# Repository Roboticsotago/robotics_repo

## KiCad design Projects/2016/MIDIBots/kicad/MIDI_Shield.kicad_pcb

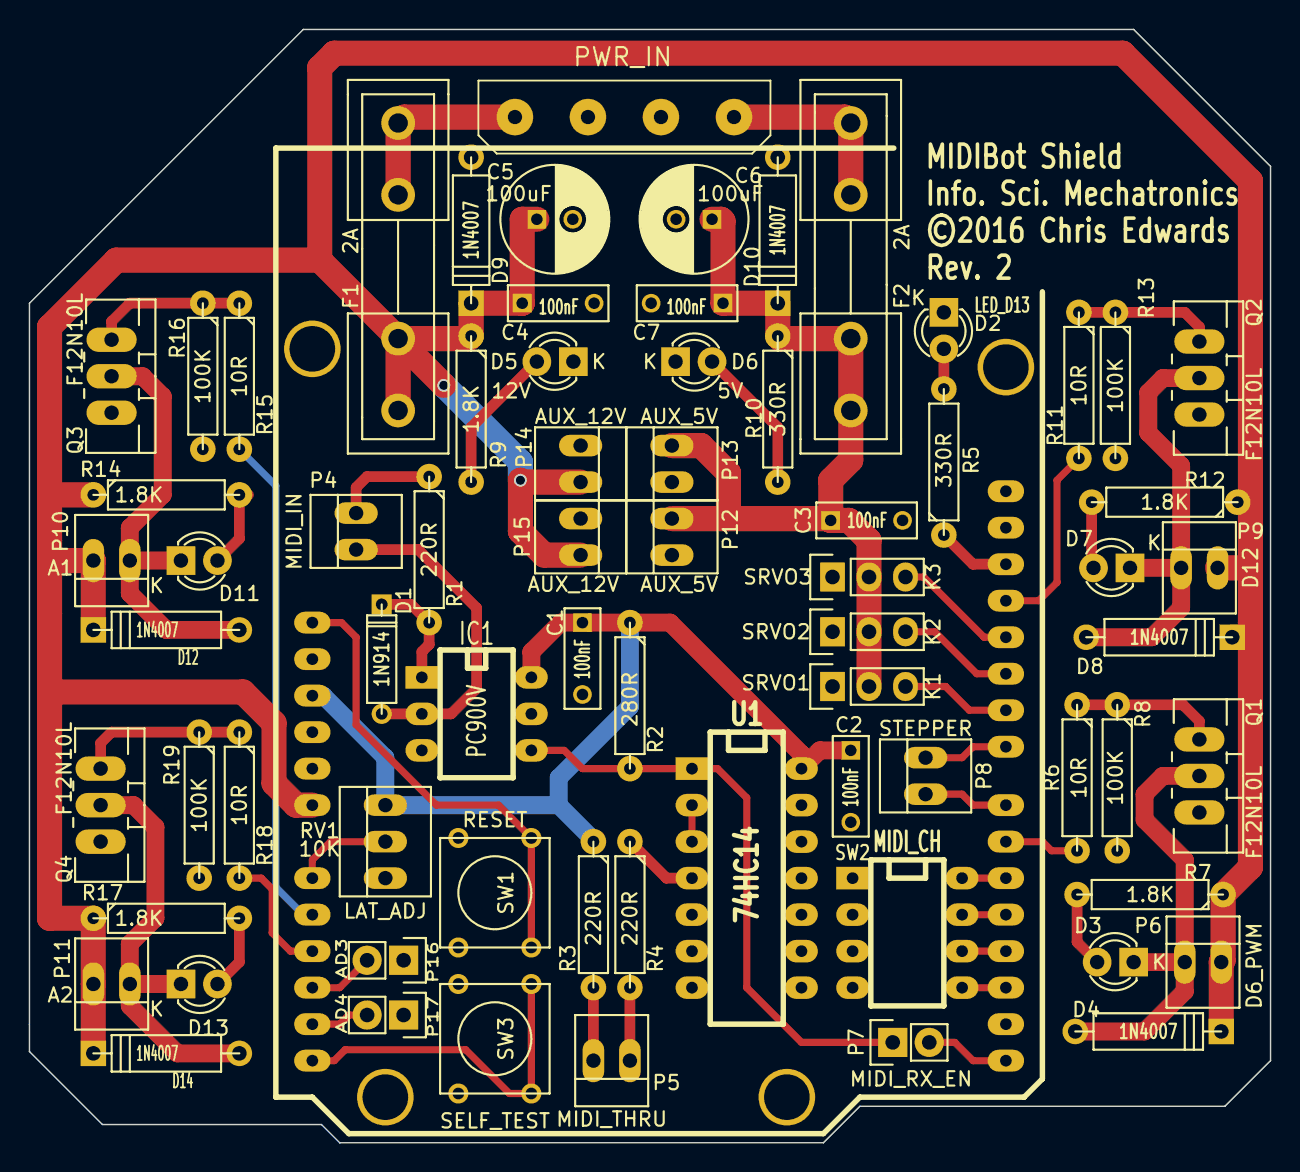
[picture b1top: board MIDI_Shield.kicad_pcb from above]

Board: 2 copper layers, 86.4 x 77.5 mm, 71 parts (0 on the bottom side), 49 nets.

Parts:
C1, C2, C3, C4, C7: 100nF; C_Rect_L7_W2.5_P5
C5, C6: 100uF; C_Radial_D7.5_L11.2_P2.5
D1: 1N914; D3
D2: LED_D13; LED-3MM
D3, D7, D11, D13: LED; LED-3MM
D4, D8, D9, D10, D12, D14: 1N4007; D4
D5: 12V; LED-3MM
D6: 5V; LED-3MM
F1, F2: 2A; Fuseholder5x20_horiz_open_inline_Type-I
IC1: PC900V; DIP-6__300_ELL
K1: SRVO1; Pin_Header_Straight_1x03
K2: SRVO2; Pin_Header_Straight_1x03
K3: SRVO3; Pin_Header_Straight_1x03
P3: PWR_IN; xess-MOLEX-8981-04P
P4: MIDI_IN; PINHEAD1-2
P5: MIDI_THRU; PINHEAD1-2
P6: D6_PWM; PINHEAD1-2
P7: MIDI_RX_EN; Pin_Header_Straight_1x02
P8: STEPPER; PINHEAD1-2
P9: D12; PINHEAD1-2
P10: A1; PINHEAD1-2
P11: A2; PINHEAD1-2
P12, P13: AUX_12V; PINHEAD1-2
P14, P15: AUX_5V; PINHEAD1-2
P16: AD3; Pin_Header_Straight_1x02
P17: AD4; Pin_Header_Straight_1x02
Q1, Q2, Q3, Q4: F12N10L; TO-220_Neutral123_Vertical_LargePads
R1, R3, R4: 220R; R4-LARGE_PADS
R2: 280R; R4-LARGE_PADS
R5, R10: 330R; R4-LARGE_PADS
R6, R11, R15, R18: 10R; R4-LARGE_PADS
R7, R9, R12, R14, R17: 1.8K; R4-LARGE_PADS
R8, R13, R16, R19: 100K; R4-LARGE_PADS
RV1: 10K; PINHEAD1-3
SHIELD1: ARDUINO_SHIELD
SW1: RESET; SW_PUSH_SMALL
SW2: MIDI_CH; DIP-8__300_ELL
SW3: SELF_TEST; SW_PUSH_SMALL
U1: 74HC14; DIP-14__300_ELL

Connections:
+5V: C3.1, C6.1, C7.1, D10.1, F2.2, K1.2, K2.2, K3.2, P14.2, P15.2, R10.1
+12V: C4.1, C5.1, D4.1, D8.1, D9.1, D12.1, D14.1, F1.1, P6.2, P9.2, P10.2, P11.2, P12.2, P13.2, R7.1, R9.1, R12.1, R14.1, R17.1, SHIELD1.V_IN
/AD3: P16.2, SHIELD1.AD3
/AD4: P17.2, SHIELD1.AD4
/LATENCY_ADJ: RV1.2, SHIELD1.AD0
/LED_BUILTIN: R5.1, SHIELD1.13
/MIDI_CH_1x: SHIELD1.2, SW2.5
/MIDI_CH_2x: SHIELD1.3, SW2.6
/MIDI_CH_4x: SHIELD1.4, SW2.7
/MIDI_CH_8x: SHIELD1.5, SW2.8
/MIDI_IN_TTL: IC1.4, P7.1, R2.2, U1.1
/MOSFET_1_PWM: R6.2, SHIELD1.6
/MOSFET_2: R11.2, SHIELD1.12
/MOSFET_3: R15.2, SHIELD1.AD1
/MOSFET_4: R18.2, SHIELD1.AD2
/RESET: SHIELD1.RST, SW1.1
/SELF_TEST: SHIELD1.AD5, SW3.1
/SERVO_1: K1.3, SHIELD1.9
/SERVO_2: K2.3, SHIELD1.10
/SERVO_3: K3.3, SHIELD1.11
/STEPPER_DIR: P8.1, SHIELD1.7
/STEPPER_STEP: P8.2, SHIELD1.8
GND: C1.2, C2.2, C3.2, C4.2, C5.2, C6.2, C7.2, D2.1, D5.1, D6.1, D9.2, D10.2, IC1.5, K1.1, K2.1, K3.1, P3.2, P3.3, P12.1, P13.1, P14.1, P15.1, P16.1, P17.1, Q1.3, Q2.3, Q3.3, Q4.3, R8.2, R13.2, R16.2, R19.2, RV1.1, SHIELD1.GND1, SHIELD1.GND2, SHIELD1.GND3, SW1.2, SW2.1, SW2.2, SW2.3, SW2.4, SW3.2, U1.5, U1.7, U1.9, U1.11, U1.13
unnamed: D1.1, IC1.1, R1.2
unnamed: D1.2, IC1.2, P4.1
unnamed: D2.2, R5.2
unnamed: D3.1, D4.2, P6.1, Q1.2
unnamed: D3.2, R7.2
unnamed: D5.2, R9.2
unnamed: D6.2, R10.2
unnamed: D7.1, D8.2, P9.1, Q2.2
unnamed: D7.2, R12.2
unnamed: D11.1, D12.2, P10.1, Q3.2
unnamed: D11.2, R14.2
unnamed: D13.1, D14.2, P11.1, Q4.2
unnamed: D13.2, R17.2
unnamed: F1.2, P3.1
unnamed: F2.1, P3.4
unnamed: P4.2, R1.1
unnamed: P5.2, R3.2
unnamed: P5.1, R4.2
unnamed: P7.2, SHIELD1.0
unnamed: Q1.1, R6.1, R8.1
unnamed: Q2.1, R11.1, R13.1
unnamed: Q3.1, R15.1, R16.1
unnamed: Q4.1, R18.1, R19.1
unnamed: R4.1, U1.4
unnamed: U1.2, U1.3
VCC: C1.1, C2.1, IC1.6, R2.1, R3.1, RV1.3, SHIELD1.5V, U1.14

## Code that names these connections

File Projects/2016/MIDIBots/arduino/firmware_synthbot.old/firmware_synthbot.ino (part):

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	MIDI_4x_PIN = 4,
	MIDI_8x_PIN = 5,
	MOSFET_PWM_PIN = 6,
	SERVO_1_PIN = 9,
	SERVO_2_PIN = 10,
	SERVO_3_PIN = 11,
	MOSFET_2_PIN = 12,
	MOSFET_3_PIN = A1, /* not A3 as on the silkscreen! */
	MOSFET_4_PIN = A2, /* not A4 as on the silkscreen! */
	LED_PIN = 13,
	LATENCY_ADJUST_PIN = A0,
	SELF_TEST_PIN = A5
;

int
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	pinMode(MIDI_8x_PIN, INPUT_PULLUP);
	
	// Ditto for self-test button:
	pinMode(SELF_TEST_PIN, INPUT_PULLUP);
	
	// TODO: output pins (servos, MOSFETs, LED)
	pinMode(LED_PIN, OUTPUT); digitalWrite(LED_PIN, LOW);
	pinMode(MOSFET_PWM_PIN, OUTPUT); analogWrite(MOSFET_PWM_PIN, 0);
	pinMode(MOSFET_2_PIN, OUTPUT); digitalWrite(MOSFET_2_PIN, LOW);
	pinMode(MOSFET_3_PIN, OUTPUT); digitalWrite(MOSFET_3_PIN, LOW);
	pinMode(MOSFET_4_PIN, OUTPUT); digitalWrite(MOSFET_4_PIN, LOW);
	pinMode(SERVO_1_PIN, OUTPUT); digitalWrite(SERVO_1_PIN, LOW);
	pinMode(SERVO_2_PIN, OUTPUT); digitalWrite(SERVO_2_PIN, LOW);
	pinMode(SERVO_3_PIN, OUTPUT); digitalWrite(SERVO_3_PIN, LOW);
	
	// Initialise MIDI channel number according to DIP switch settings:
	read_MIDI_channel();
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	clearData();
	
	// Attach interrupt for self-test button and function:
//	attachInterrupt(digitalPinToInterrupt(SELF_TEST_PIN), self_test, FALLING);
	// Only available on certain pins?  Just poll in main loop instead.
	
	// Flash to indicate startup/ready:
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
void loop()
{
	if (!digitalRead(SELF_TEST_PIN)) {
		self_test();
	}
	process_MIDI();
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}

void test_button() {
	digitalWrite(LED_PIN, !digitalRead(SELF_TEST_PIN));
}

void test_flash_number() {
	if (!digitalRead(SELF_TEST_PIN)) {
		flash_number(3);
		delay(2000);
		flash_number(16);
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}

void test_MIDI_channel() {
	if (!digitalRead(SELF_TEST_PIN)) {
		read_MIDI_channel();
		Serial.println(MIDI_channel);
		flash_number(MIDI_channel);
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}

void test_MOSFETs() {
	if (!digitalRead(SELF_TEST_PIN)) {
		analogWrite(MOSFET_PWM_PIN, 64);
		digitalWrite(MOSFET_2_PIN, HIGH);
		digitalWrite(MOSFET_3_PIN, HIGH);
		digitalWrite(MOSFET_4_PIN, HIGH);
	} else {
		analogWrite(MOSFET_PWM_PIN, 0);
		digitalWrite(MOSFET_2_PIN, LOW);
		digitalWrite(MOSFET_3_PIN, LOW);
		digitalWrite(MOSFET_4_PIN, LOW);
	}
}

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	delay(250);
	digitalWrite(MOSFET_PWM_PIN, LOW);
	
	digitalWrite(MOSFET_2_PIN, HIGH);
	delay(250);
	digitalWrite(MOSFET_2_PIN, LOW);
	
	digitalWrite(MOSFET_3_PIN, HIGH);
	delay(250);
	digitalWrite(MOSFET_3_PIN, LOW);

	digitalWrite(MOSFET_4_PIN, HIGH);
	delay(250);
	digitalWrite(MOSFET_4_PIN, LOW);
}

void test_PWM() {
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
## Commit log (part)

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2017-06-11 Added Arduino Mega drilling pattern
2017-06-13 Updated IR sensor code to work with analog inputs.
2017-06-13 Added atan2() demo in C
2017-06-13 Added returncode (to avoid `make` throwing an error when building)
2017-06-14 Added Arduino version of the atan2() demo program
2017-06-14 Fixed castor shim height (after actually measuring the actual castor height and robot platform height!)
2017-06-15 SoccerBot kicker paddle: reduced hole size to help grip 3.5 mm machine screws
2017-06-15 Expanded to-do list, added a Pure Data patch demonstrating how to pipe data in from Arduino serial stream
2017-06-15 Stripped out Chris's code for determining IR ball angle and distance the students to fill in.
2017-06-15 Added some notes on the Raspberry Pi camera
2017-06-15 Refined dimensions of RPi camera housing
2017-06-16 Add DSPace Robot board mounting pattern
2017-06-16 SoccerBot block diagram added
2017-06-16 Added notes on the Power HD DSM44 digital servo motor
2017-06-16 SoccerBots: added simple kicker mounting hinge part
2017-06-16 Added prototype kicker linkage part
2017-06-17 Lengthened kicker paddle for top-mounted servo
2017-06-17 Corrected servo mount dimensions for DSM44 servo; rounded corners
2017-06-18 Added servo horn extension part
2017-06-19 Added Dspace motor intial controller
2017-06-19 Added initial design for replacement mount for Tamiya castor
2017-06-19 Servo mount: reduced servo mounting hole diameter
2017-06-20 Adjusted range of servo, serial changes
2017-06-20 Added cylindrical spacer for mounting the IR platform on the main chassis
2017-06-20 Reduced mounting hole size to suit M3 screws (hopefully)
2017-06-21 Added software pipeline for mega
2017-06-21 Renamed IR_test to Sensors
2017-06-21 Renamed motor control
2017-06-22 Removed redundant Dalek code in SoccerBot motor control script.
    Fixed indentation & attempted a fix of Servo toggle switch.
2017-06-22 Corrected spelling error :-D
2017-06-22 Updated magnetometer test to point towards any heading
2017-06-22 Changed camera res
2017-06-22 have debugging mode output less often
2017-06-22 Added range sensor to sensor program
2017-06-22 changed PWM thresholds
2017-06-22 changed deadzone thresholds.
2017-06-23 Added symbolic link
2017-06-23 Added wrapper script for running the Mega sensor cu pipeline (so it can be restarted by monit if necessary
2017-06-26 Added initial debriefing notes from the Otago 2017 regionals
2017-06-26 Added further explanation on motor KV rating
2017-06-27 Added separate program for camera calabration
2017-06-27 Added motor control for boris
2017-06-29 Some tidying of EEPROM doc
2017-06-29 Added (OLD) camera_calibration_state.py file from the netbook
2017-06-30 Added a few extras for Friday's plan
2017-06-30 Fixed range sensor behaviour (after setting jumpers and programming its EEPROM for passive PWM mode)
2017-06-30 Switching over to use Tcl-based read_sensors.tcl instead of cu; added message between main control patch (bot-specific) to motor-control.pd to command which serial port to use for driving
2017-07-04 Converted document on Arduino memory and EEPROM use to Markdown
2017-07-04 main programme for goalie and running different pd script depending on the robot
2017-07-04 slider for controlling both motors
2017-07-04 Conditional code to use appropriate serial device for sensing depending on the robot
2017-07-04 Reports which robot is being used
2017-07-04 Arduino EEPROM demo program: reformatted, added use of compile-time E2END for EEPROM size, have EEPROM dump include the address for each byte.
2017-07-04 Simplified EEPROM_read_int() declarations
2017-07-04 Arduino memory doc: added description of E2END
2017-07-06 Added Tcl code demonstrating signal handling
2017-07-06 Added .pyc, .o, .a to .gitignore
2017-07-06 SoccerBots to-do list update
2017-07-06 Corrected motor serial device for attacker SoccerBot
2017-07-06 Changed SoccerBots blob_tracking.py symlink to point to relative path
2017-07-06 Added *.save pattern to top-level .gitignore
2017-07-06 Redundant update to SoccerBot DSpace servo motor test program, adding commented note to refer to new program location
2017-07-06 Added to-do note for read_sensors.tcl
2017-07-06 Added note about using #if rather than #ifdef for things like DEBUGGING==1
2017-07-07 Removed some unnecessary comments (see robotics_repo/Documentation/Tcl/serial-basics.tcl instead), rearranged output messages
2017-07-07 Magnetometer now uses EEPROM for calibration
2017-07-07 Read sensors attemps reconnection upon serial disconnect
2017-07-10 working on commands to open each different programme in its own terminal
2017-07-10 new arduino file to play nokia tune for startup
2017-07-10 Made restarteverything.sh executabl
2017-07-10 added function for getting note durations from tempo, added pokemon song :)
2017-07-11 Some changes to IR sensor shroud cone
2017-07-12 Added document explaining the use of until loops in the shell to reliably start a command
2017-07-12 changed buzzer.ino so you need a separate h file to include the notes for each tune (and made 3 different h files with different songs)
2017-07-14 Tweaked thresholds and added comments for goalie
2017-07-16 Redesigned servo mount to be more compact, include slot for cabling
2017-07-17 Added conditional code to ignore rear IR sensors on goalie; added short (microseconds) delay in ultrasonic range sensor code
2017-07-25 Implemented automatic gain control with thresholded culling of weak IR readings, hoping to improve handling of ball reflections in the goal. Also removed redundant 'count' variable, and restored IR s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
2017-07-28 Added reflectance sensing from Tobias's work (for detecting whether in goal area)
2017-08-01 Converted goalie control to mostly use signals; refinements to sig2num~
2017-08-04 pd now starts with DSP on
2017-08-10 added hole for push button, added construction lines for larger servo and created range sensor mount
2017-08-22 added nokia tune for startup
2017-08-28 Latest refinements to SoccerBot chassis, specifically hollowing out more the mounting pillars for the top platform, adding a recess for the main power switch, and slightly enlarging the holes for the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
2017-08-29 Added seperate servo limits for robots, removed servo midpoint
2017-08-29 Fixed (we think) problem with DSpace motor control program causing the kicker to operate when it shouldn't, by casting the result of Serial.read() to an (unsigned byte). Also rearranged some #defines.
2017-08-29 Unspecified changes to goalie_control.pd
2017-08-29 Adjusted tests in motor-test.tcl to toggle the least-significant bit to ensure it doesn't cause the kicker to operate accidentally
2017-08-29 motor-test.tcl now tests motors at full speed
2017-08-29 Added kicker flapping to signal startup
2017-08-30 Updated to-do list
2017-08-30 motor-test.tcl: added reminder to turn on the motor switch!
2017-08-30 SoccerBots: added notes about adding a low-battery warning circuit
2017-09-01 Flipped actual and readings around
2017-09-01 filtered compass, vision system input. Also added speedlim
2017-09-01 slowed downthrottle speed & steering in shoot mode
2017-09-01 removed redundant display objects to hopefully speed up xsession
2017-09-02 added frame rate calculations and delays.
2017-09-02 adding scaling factor
2017-09-02 filtered out -180 for vision system
2017-09-05 Changed boris duty, tidied up motor-control.pd
2017-09-05 Disable graph-on-parent for sig2num~
2017-09-05 Tweaked goalie settings for steering while reversing, and added some to-do items (enable kicker, implement proper modes as we have for Shutter).
2017-09-07 Added a couple of to-do items for Shutter control Pd program
2017-09-08 SoccerBots: added file itemising improvements since the regional competition
2017-09-08 changed deadzones so robots don't drive quite so fast
2017-09-08 major changes to attacker logic
2017-09-08 fixed goalie intercept routine
2017-09-10 Tobias's changes to Shutter from Sunday, plus some tidying
2017-09-10 changed deadzones for Boris
2017-09-12 changed default sampling speed to a much faster sampling speed
2017-09-12 added not patch
2017-09-12 changes for seek and shoot mode
2017-09-13 Downgraded serial speed
2017-09-14 Added signal version of 'not' for Pd
2017-09-14 SoccerBots motor-control.pd: removed print from kick
2017-09-14 Added Tcl code fragments for a GUI-based test of the DSpace board
2017-09-14 Increased baud rate to 19200
2017-09-14 Some useful tweaks to attacker program, including allowing it to move backwards while seeking depending on which way it's facing, and tweaking the various constants for seek and aim mode. Also added 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
2017-09-15 Made bizarro modifications to runeverything.sh to get vision system working at startup.
2017-09-15 tweaked values for aim mode for better turn around ball
2017-09-15 Changed Boris's servo limits for new servo
2017-09-15 Boris now has panic and stuck mode
2017-09-19 Added Python script testing/demonstrating the use of the picamera library
2017-09-21 Added notes on installing OpenCV with Python bindings
2017-09-21 Added shorter version of the Mountain King melody
2017-09-21 Added basic usable raspivid command line example
2017-09-26 cv2 blob tracking: now samples from a smaller rectangle within the image (drawn over the image to help with targetting), and for longer
2017-10-10 working on blob tracking 2.0: added code to find largest blob and lines to show centre of blob
2017-10-18 Added initial candidate parts list for the 3D printer project
2017-10-18 Add centrelines for X-Y plotter sketch
2017-10-20 pictures of cube and its pieces
2017-10-27 Updated log
2017-10-31 Added formula for calculating stepper motor resonant frequency
2017-10-31 Added notes on gearing and Wade's extruder for comparison
2017-11-03 working on cube design
2017-11-07 added tile cutouts onto cube pieces
2017-11-10 removed tiles from pieces
2017-11-21 Added notes from Charles Steinkuehler on BBB step rates
2017-12-01 updated stepper motor test sketch
2018-04-03 sherlock
2018-04-06 added ball distance from hitechnic sensor
2018-04-17 chaged scale factors for hollow bits
2018-04-20 round mode workingls!
2018-04-24 changed to in all pieces, re-exported pieces and added in holes for the motor into the core
2018-05-01 exported tile
2018-05-08 slight change of design - thinner face on core & exported edge in halves
2018-05-13 Added link to electrical-symbols.com's index of PDFs of electronic symbols
2018-05-25 FIXED EVERYTHING&stuff Tob/Hen afternoon robot stuff
2018-05-29 corrected hall effect sensor code
    fixed previously missing setup of pinMode
2018-06-01 got rid of redundant ir seeker code to fix everything
2018-06-01 added cv2 calibration code
2018-06-05 working on a cube assembly in openscad
2018-06-08 changed speeds and generally improved shoot mode
2018-06-15 adjusted start-up time of sensor_input to allow time for PureData startup
2018-06-19 copied stuck code from shutter to boris
2018-07-06 started python script for boris
2018-07-17 minor changes
2018-08-10 added main loop sequence, wrote code for homing (issues surrounding robot wheels rubbing on chassis), generally improved boris python code. TODO: sort out index error
2018-09-19 Added some notes on stepper motors
2018-09-19 Expanded 3D printer ideas file, including leadscrew specs and example machines on YouTube
2018-09-19 Rubik: added notes on motor sizes
2018-10-09 added attacker stuff post-nationals 2018
2018-10-18 RPi pinout: implemented colour scheme, added additional function labels
2018-10-23 3D printer: updated possible parts, 2018-09-20
2019-02-26 Added lesson plans
2019-03-04 3D printer: expanded performance.txt
2019-03-05 3D printer: add Adafruit 36T GT2 pulley
2019-03-05 3D printer: motor and drive parameters: switch to conditional formatting
2019-04-09 changed design of cube pieces - now hollow with tiles to be pressed in
2019-04-23 changed hole size to 2mm diam
2019-05-07 added holes to centre connector piece and made holes proper length
2019-05-13 redoing stuff to make code nicer and naming more consistent
2019-05-14 did more stuff
2019-05-21 stepper test arduino code
2019-05-28 stuff
2019-08-09 Add edge_connector parts from the lab

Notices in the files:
Projects/2016/MIDIBots/kicad/MIDI_Shield.kicad_pcb:
©2016 Chris Edwards
